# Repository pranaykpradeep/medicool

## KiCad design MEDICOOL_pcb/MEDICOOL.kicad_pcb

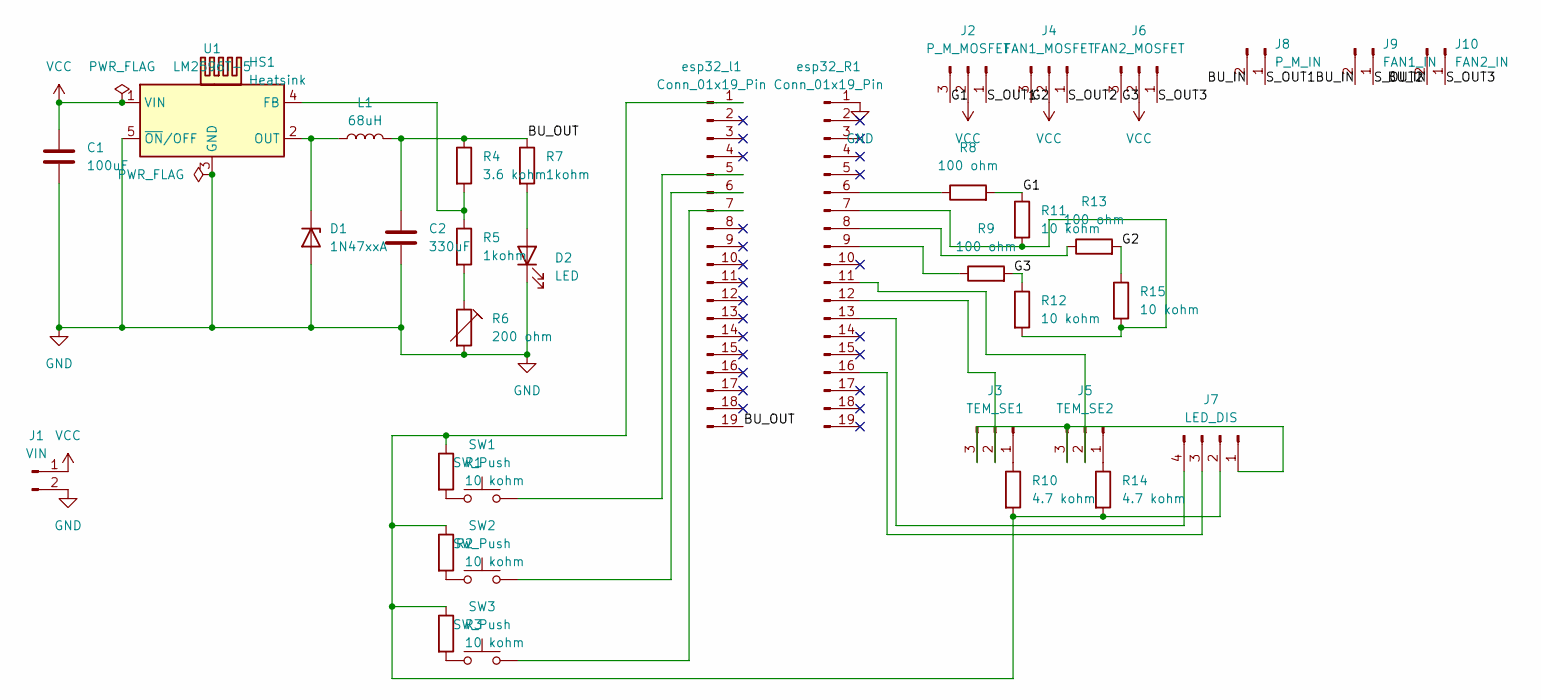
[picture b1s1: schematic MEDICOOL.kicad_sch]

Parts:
C1: 100uF; CP_Radial_D8.0mm_P3.50mm
C2: 330uF; CP_Radial_D8.0mm_P3.50mm
D1: 1N47xxA; D_DO-41_SOD81_P10.16mm_Horizontal
D2: LED; LED_D5.0mm
HS1: Heatsink; Heatsink_Fischer_FK224xx2201_25x8.3mm
J1: VIN; PinHeader_1x02_P2.54mm_Vertical
J2: P_M_MOSFET; FanPinHeader_1x03_P2.54mm_Vertical
J3: TEM_SE1; PinHeader_1x03_P2.54mm_Vertical
J4: FAN1_MOSFET; FanPinHeader_1x03_P2.54mm_Vertical
J5: TEM_SE2; PinHeader_1x03_P2.54mm_Vertical
J6: FAN2_MOSFET; FanPinHeader_1x03_P2.54mm_Vertical
J7: LED_DIS; PinHeader_1x04_P2.54mm_Vertical
J8: P_M_IN; PinHeader_1x02_P2.54mm_Vertical
J9: FAN1_IN; PinHeader_1x02_P2.54mm_Vertical
J10: FAN2_IN; PinHeader_1x02_P2.54mm_Vertical
L1: 68uH; L_Axial_L14.5mm_D5.8mm_P20.32mm_Horizontal_Fastron_HBCC
R1, R2, R3, R11, R12, R15: 10 kohm; R_Axial_DIN0204_L3.6mm_D1.6mm_P7.62mm_Horizontal
R4: 3.6 kohm; R_Axial_DIN0204_L3.6mm_D1.6mm_P7.62mm_Horizontal
R5, R7: 1kohm; R_Axial_DIN0204_L3.6mm_D1.6mm_P7.62mm_Horizontal
R6: 200 ohm; Potentiometer_ACP_CA6-H2,5_Horizontal
R8, R9, R13: 100 ohm; R_Axial_DIN0204_L3.6mm_D1.6mm_P7.62mm_Horizontal
R10, R14: 4.7 kohm; R_Axial_DIN0204_L3.6mm_D1.6mm_P7.62mm_Horizontal
SW1, SW2, SW3: SW_Push; SW_PUSH_6mm
U1: LM2596T-5; TO-220-5_P3.4x3.7mm_StaggerOdd_Lead3.8mm_Vertical
esp32_R1, esp32_l1: Conn_01x19_Pin; PinHeader_1x19_P2.54mm_Vertical

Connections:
/BU_IN: J8.2, J9.2, J10.2
/BU_OUT: C2.1, L1.2, R4.1, R7.1, esp32_l1.19
/G1: J2.3, R8.2, R11.1
/G2: J4.3, R13.2, R15.1
/G3: J6.3, R9.2, R12.1
/S_OUT1: J2.1, J8.1
/S_OUT2: J4.1, J9.1
/S_OUT3: J6.1, J10.1
GND: C1.2, C2.2, D1.2 (A), D2.1 (K), J1.2, R6.2, U1.3 (GND), U1.5 (~ON/OFF), esp32_R1.1
unnamed: D1.1 (K), L1.1, U1.2 (OUT)
unnamed: D2.2 (A), R7.2
unnamed: J3.1, R10.1
unnamed: J3.2, esp32_R1.12
unnamed: J3.3, J5.3, J7.1
unnamed: J5.1, R14.1
unnamed: J5.2, esp32_R1.11
unnamed: J7.2, R1.1, R2.1, R3.1, R10.2, R14.2, esp32_l1.1
unnamed: J7.3, esp32_R1.16
unnamed: J7.4, esp32_R1.13
unnamed: R1.2, SW1.1
unnamed: R2.2, SW2.1
unnamed: R3.2, SW3.1
unnamed: R5.2, R6.1
unnamed: R4.2, R5.1, U1.4 (FB)
unnamed: R8.1, esp32_R1.6
unnamed: R11.2, R12.2, R15.2, esp32_R1.7
unnamed: R13.1, esp32_R1.8
unnamed: R9.1, esp32_R1.9
unnamed: SW1.2, esp32_l1.5
unnamed: SW2.2, esp32_l1.6
unnamed: SW3.2, esp32_l1.7
VCC: C1.1, J1.1, J2.2, J4.2, J6.2, U1.1 (VIN)

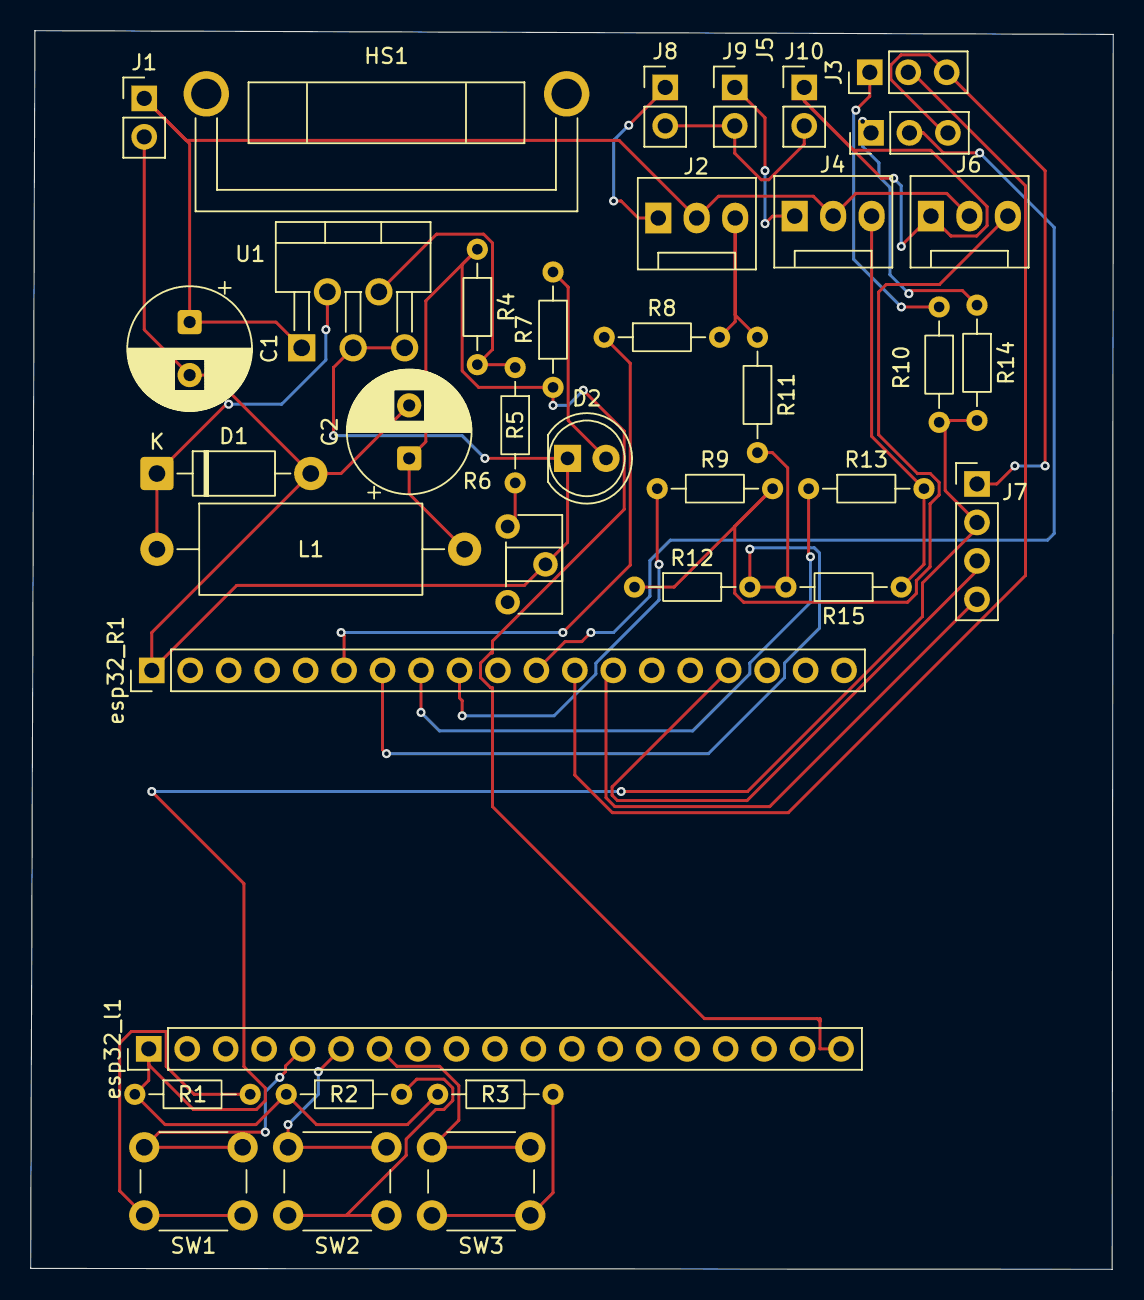
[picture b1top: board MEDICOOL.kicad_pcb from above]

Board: 2 copper layers, 71.5 x 81.8 mm, 37 parts (0 on the bottom side), 32 nets.
